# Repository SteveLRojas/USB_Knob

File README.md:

# USB_Knob
A USB knob that can scroll, pan, adjust the volume, and more. Uses the CH552 USB microcontroller.

## What does it do?
This device is a computer peripheral, it can scroll, pan (scroll horizontally), and adjust the volume. It also has simple media controls such as play/pause, next, and prev.  

## How does it work?
The device has 3 buttons: left, center, and right. These 3 buttons are used to set the "mode" of the device, and when they are held down they act as function modifiers. The device also has a knob which has a fourth button, and is the most frequently used control on the device. Three indicator LEDs indicate the current "mode" setting of the device.  

## Device features
### Scroll mode
- Press the left button to enter scroll mode.  
- The knob button functions as the middle mouse button.  
- While the left button is released spinning the knob scrolls vertically (like a mouse wheel).  
- While the left button is pressed spinning the knob adjusts the scrolling speed (the speed range is 1 to 10).  
### Pan mode
- Press the center button to enter pan mode.  
- If the mouse wiggler feature is enabled (option set at compile time) the knob button toggles the mouse wiggler on/off. The mouse wiggler only acts when the knob is in pan mode, but the on/off state is maintained even when the device is in a different mode.  
- If the mouse wiggler feature is not enabled then the knob button functions as the middle mouse button.  
- While the center button is released spinning the knob scrolls horizontally.  
- While the center button is pressed spinning the knob adjusts the scrolling (pan) speed (the range is 1 to 10).  
### Volume mode
- Press the right button to enter volume mode.  
- While the right button is released the knob button acts as a mute button.  
- While the right button is pressed the knob button acts as a play/pause button.  
- While the right button is released spinning the knob adjusts the volume.  
- While the right button is pressed spinning the knob functions as media next/prev buttons.

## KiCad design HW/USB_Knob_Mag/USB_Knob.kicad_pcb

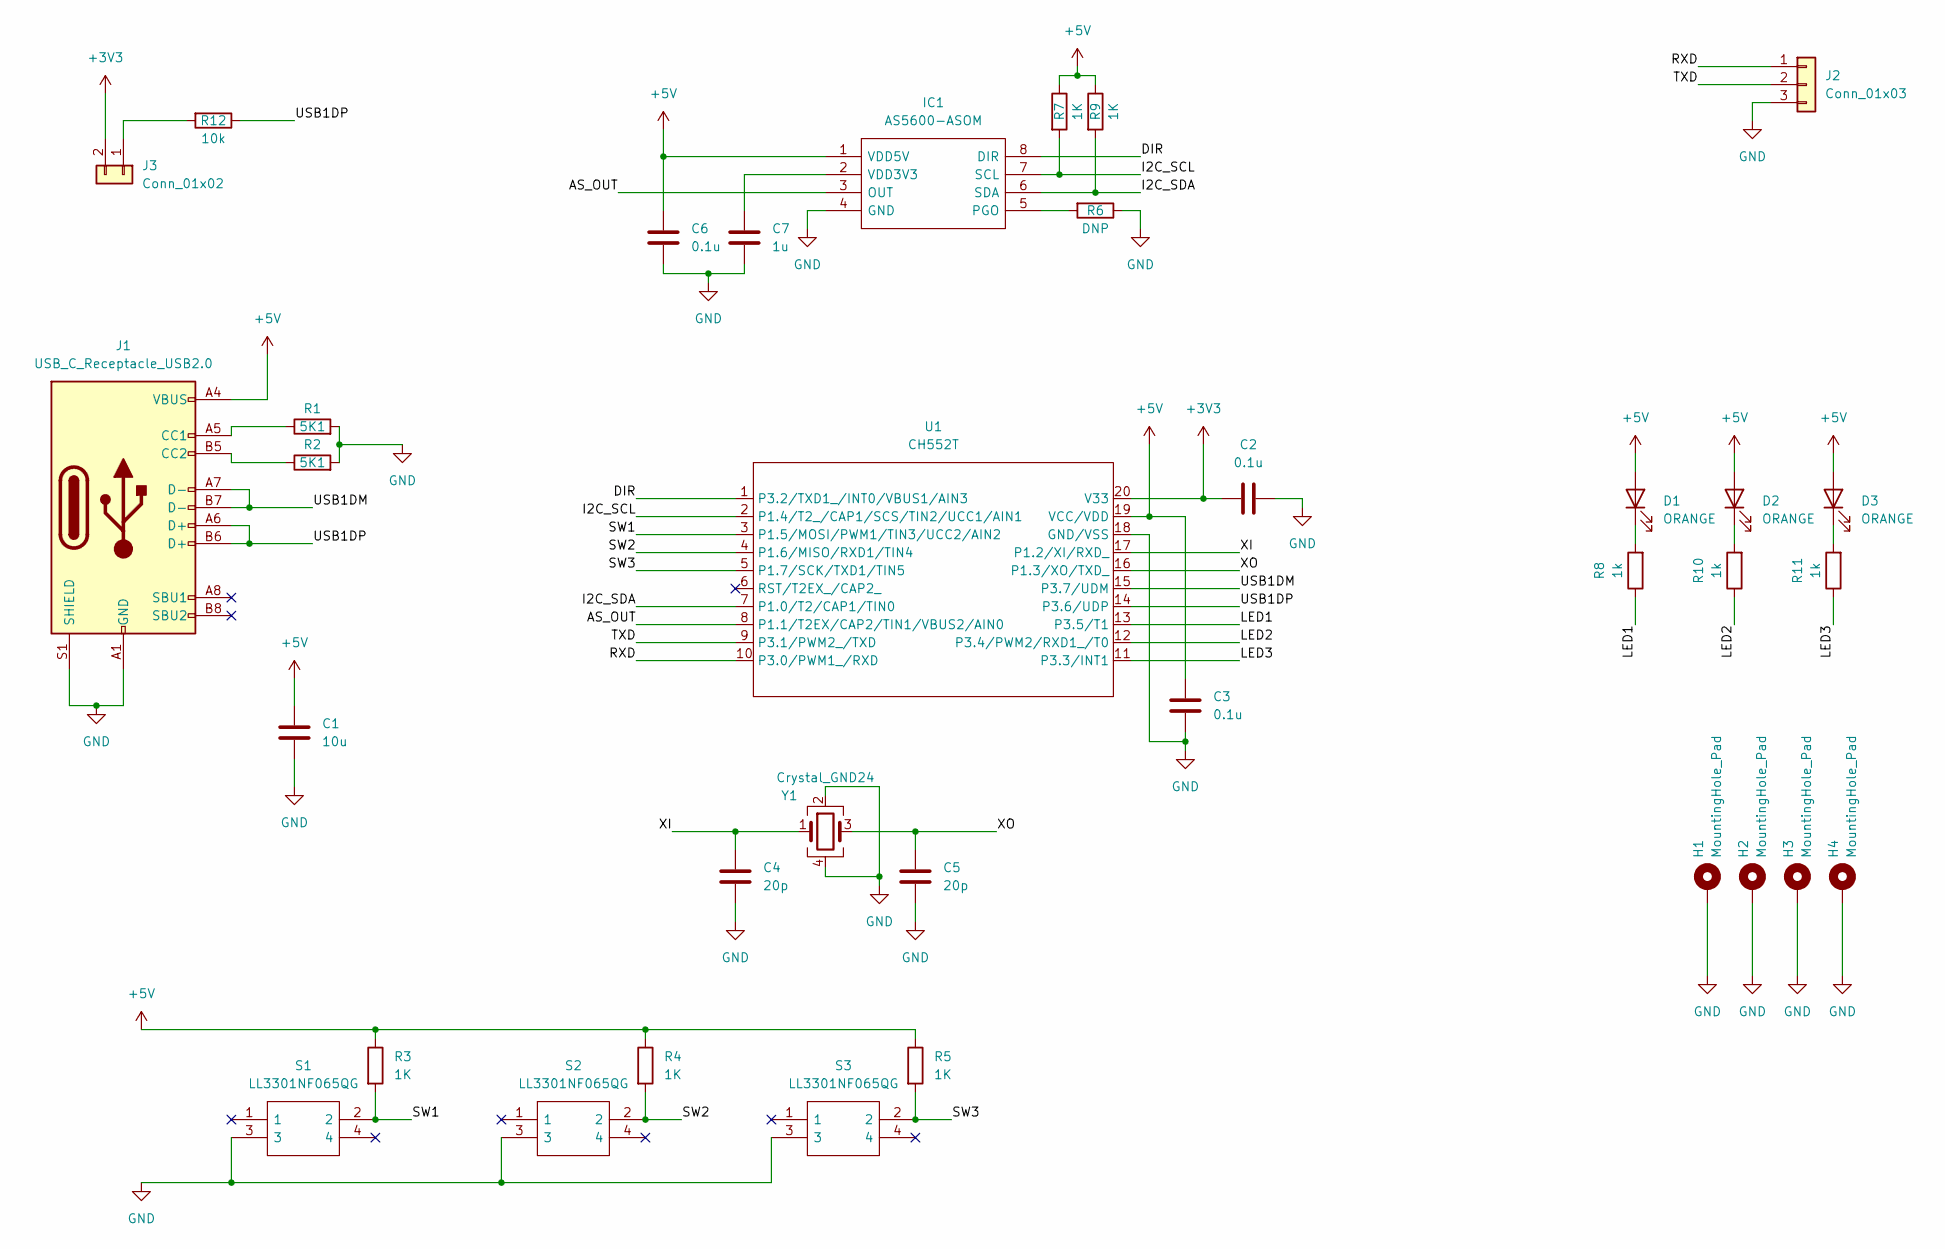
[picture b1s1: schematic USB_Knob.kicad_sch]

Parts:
C1: 10u; C_1206_3216Metric
C2, C3, C6: 0.1u; C_0805_2012Metric
C4, C5: 20p; C_0805_2012Metric
C7: 1u; C_0805_2012Metric
D1, D2, D3: ORANGE; LED_0805_2012Metric
H1, H2, H3, H4: MountingHole_Pad; MountingHole_3.2mm_M3_Pad
IC1: AS5600-ASOM; SOIC127P600X175-8N; Mouser Part Number 985-AS5600-ASOM
J1: USB_C_Receptacle_USB2.0; USB_C_Receptacle_HRO_TYPE-C-31-M-12
J2: Conn_01x03; PinHeader_1x03_P2.54mm_Horizontal
J3: Conn_01x02; PinHeader_1x02_P2.54mm_Horizontal
R1, R2: 5K1; R_0805_2012Metric
R3, R4, R5, R7, R9: 1K; R_0805_2012Metric
R6: DNP; R_0805_2012Metric
R8, R10, R11: 1k; R_0805_2012Metric
R12: 10k; R_0805_2012Metric
S1, S2, S3: LL3301NF065QG; Mouser Part Number 612-LL3301NF065QG
U1: CH552T; TSSOP-20_4.4x6.5mm_P0.65mm
Y1: Crystal_GND24; Crystal_SMD_3225-4Pin_3.2x2.5mm

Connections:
+3V3: C2.1, J3.2, U1.20 (V33)
+5V: C1.1, C3.2, C6.2, D1.2 (A), D2.2 (A), D3.2 (A), IC1.1 (VDD5V), J1.A4 (VBUS), J1.A9 (VBUS), J1.B4 (VBUS), J1.B9 (VBUS), R3.1, R4.1, R5.1, R7.1, R9.1, U1.19 (VCC/VDD)
/AS_OUT: IC1.3 (OUT), U1.8 (P1.1/T2EX/CAP2/TIN1/VBUS2/AIN0)
/DIR: IC1.8 (DIR), U1.1 (P3.2/TXD1_/INT0/VBUS1/AIN3)
/I2C_SCL: IC1.7 (SCL), R7.2, U1.2 (P1.4/T2_/CAP1/SCS/TIN2/UCC1/AIN1)
/I2C_SDA: IC1.6 (SDA), R9.2, U1.7 (P1.0/T2/CAP1/TIN0)
/LED1: R8.1, U1.13 (P3.5/T1)
/LED2: R10.1, U1.12 (P3.4/PWM2/RXD1_/T0)
/LED3: R11.1, U1.11 (P3.3/INT1)
/RXD: J2.1, U1.10 (P3.0/PWM1_/RXD)
/SW1: R3.2, S1.2, U1.3 (P1.5/MOSI/PWM1/TIN3/UCC2/AIN2)
/SW2: R4.2, S2.2, U1.4 (P1.6/MISO/RXD1/TIN4)
/SW3: R5.2, S3.2, U1.5 (P1.7/SCK/TXD1/TIN5)
/TXD: J2.2, U1.9 (P3.1/PWM2_/TXD)
/USB1DM: J1.A7 (D-), J1.B7 (D-), U1.15 (P3.7/UDM)
/USB1DP: J1.A6 (D+), J1.B6 (D+), R12.1, U1.14 (P3.6/UDP)
/XI: C4.2, U1.17 (P1.2/XI/RXD_), Y1.1
/XO: C5.2, U1.16 (P1.3/XO/TXD_), Y1.3
GND: C1.2, C2.2, C3.1, C4.1, C5.1, C6.1, C7.1, H1.1, H2.1, H3.1, H4.1, IC1.4 (GND), J1.A1 (GND), J1.A12 (GND), J1.B1 (GND), J1.B12 (GND), J1.S1 (SHIELD), J2.3, R1.2, R2.2, R6.1, S1.3, S2.3, S3.3, U1.18 (GND/VSS), Y1.2, Y1.4
unnamed: C7.2, IC1.2 (VDD3V3)
unnamed: D1.1 (K), R8.2
unnamed: D2.1 (K), R10.2
unnamed: D3.1 (K), R11.2
unnamed: IC1.5 (PGO), R6.2
unnamed: J1.A5 (CC1), R1.1
unnamed: J1.B5 (CC2), R2.1
unnamed: J3.1, R12.2

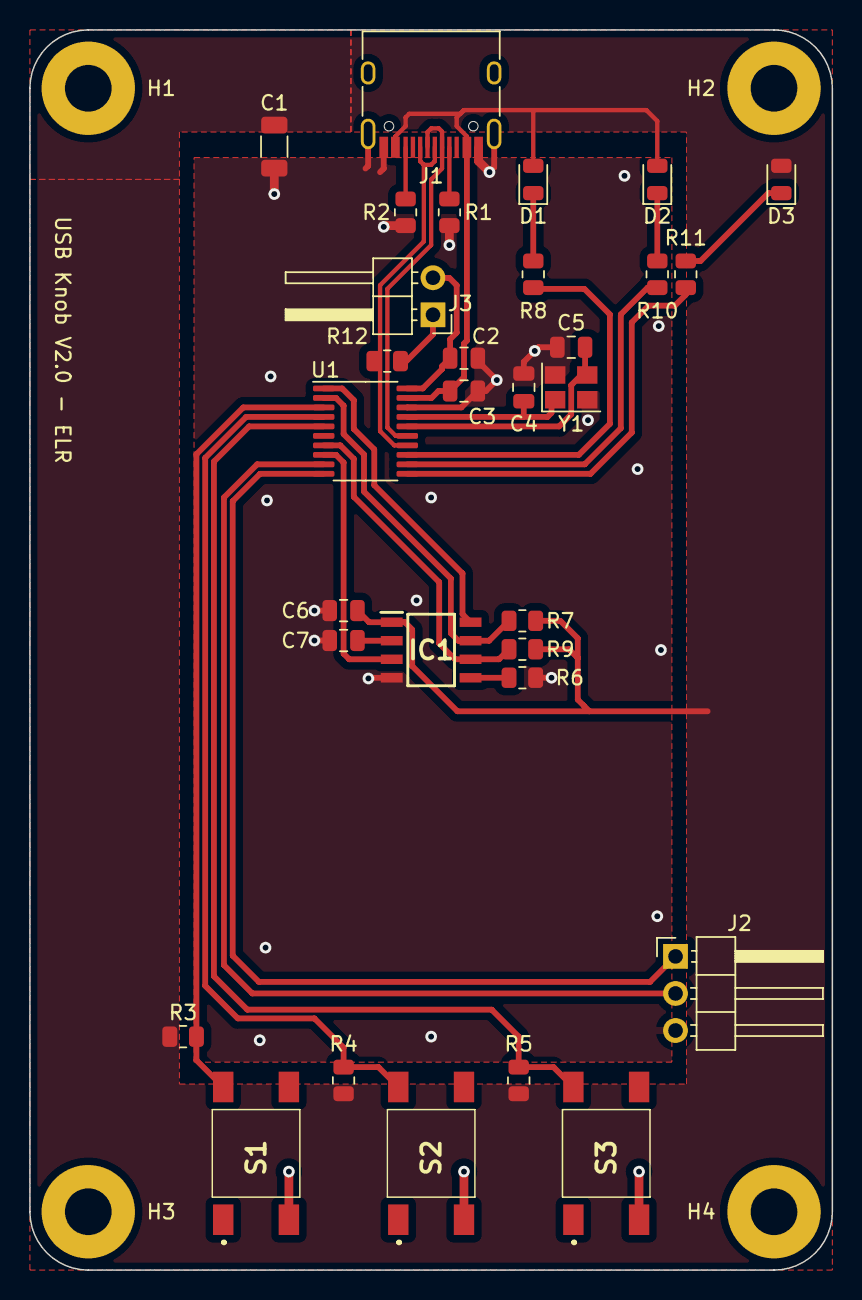
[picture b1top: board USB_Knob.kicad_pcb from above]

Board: 2 copper layers, 55.0 x 85.0 mm, 35 parts (0 on the bottom side), 27 nets.

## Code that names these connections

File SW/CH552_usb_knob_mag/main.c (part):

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	
	rcc_set_clk_freq(RCC_CLK_FREQ_24M);
	
	gpio_set_mode(GPIO_MODE_INPUT, GPIO_PORT_1, GPIO_PIN_1 | GPIO_PIN_5 | GPIO_PIN_6 | GPIO_PIN_7);	//AS_OUT, SW1, SW2, SW3
	gpio_set_mode(GPIO_MODE_OD, GPIO_PORT_1, GPIO_PIN_0 | GPIO_PIN_4);	//I2C_SDA, I2C_SCL
	gpio_set_mode(GPIO_MODE_PP, GPIO_PORT_3, GPIO_PIN_1 | GPIO_PIN_2 | GPIO_PIN_3 | GPIO_PIN_4 | GPIO_PIN_5);	//TXD, DIR, LED3, LED2, LED1
	gpio_set_mode(GPIO_MODE_INPUT, GPIO_PORT_3, GPIO_PIN_0);	//RXD
	gpio_clear_pin(GPIO_PORT_3, GPIO_PIN_2);	//Drive DIR low
	
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	rcc_reload_wdog(0x00);
	rcc_set_wdog_rst_en(RCC_WDOG_ENABLED);
	
	gpio_clear_pin(GPIO_PORT_3, GPIO_PIN_5);	//turn on LED1
	sw1_state = gpio_read_pin(GPIO_PORT_1, GPIO_PIN_5);
	sw2_state = gpio_read_pin(GPIO_PORT_1, GPIO_PIN_6);
	sw3_state = gpio_read_pin(GPIO_PORT_1, GPIO_PIN_7);
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
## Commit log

2024-10-05 Added play/pause feature, updated readme
2025-06-12 Added HW design files for version 2.0
2025-06-12 Use RCC library, updated GPIO library, wiggler now always resumes immediately
2025-07-04 Created test firmware for mag version
2025-07-05 Completed preliminary firmware for mag version
2025-07-05 Updated CC_PAN_MOUSE header
2025-09-19 Mag: Adjusted FINE_SHIFT parameter, allow mode to wrap, wiggler works in scroll mode
2025-09-22 Updated releases
2025-11-13 Added 3D models for mag version, updated releases
2025-11-13 Fixed inverted pan direction (mag)
2025-12-18 Added license
